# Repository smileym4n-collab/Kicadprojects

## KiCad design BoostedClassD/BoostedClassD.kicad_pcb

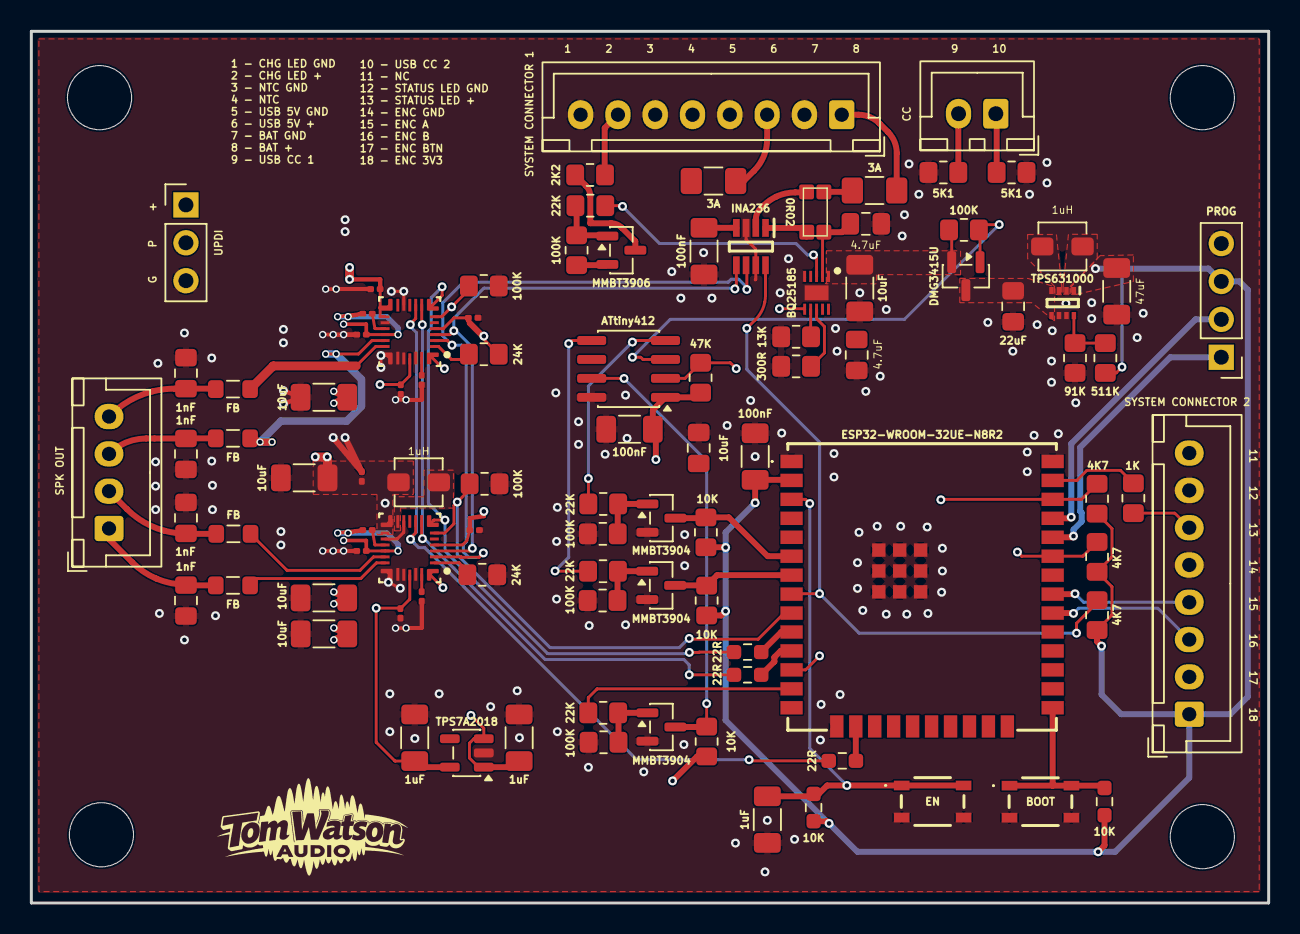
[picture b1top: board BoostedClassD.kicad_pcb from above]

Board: 4 copper layers, 82.9 x 58.4 mm, 99 parts (0 on the bottom side), 72 nets.

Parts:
C1: 22uF; C_0805_2012Metric_Pad1.18x1.45mm_HandSolder
C2: 47uF; C_1206_3216Metric_Pad1.33x1.80mm_HandSolder
C3, C7, C8: 100nF; C_1206_3216Metric_Pad1.33x1.80mm_HandSolder
C4, C5, C6: 1uF; C_1206_3216Metric_Pad1.33x1.80mm_HandSolder
C9, C10, C11, C12, C25: 10uF; C_1206_3216Metric_Pad1.33x1.80mm_HandSolder
C13, C14, C17, C18: 100nF; C_0201_0603Metric
C15, C16, C19, C20: 1uF; C_0201_0603Metric
C21, C22, C23, C24: 2.2uF; C_0201_0603Metric
C26, C27: 4.7uF; C_0805_2012Metric_Pad1.18x1.45mm_HandSolder
C28, C29, C30, C31: 1nF; C_0805_2012Metric_Pad1.18x1.45mm_HandSolder
C32: 10uF; C_0805_2012Metric_Pad1.18x1.45mm_HandSolder
F1, F2: 3A; Fuse_1206_3216Metric_Pad1.42x1.75mm_HandSolder
FB1, FB2, FB3, FB4: FB; L_0805_2012Metric_Pad1.05x1.20mm_HandSolder
H1, H2, H3, H4: MountingHole_4.3mm_M4
IC1: BQ25185; BQ25185DLHR
IC2: ESP32-WROOM-32UE-N8R2; ESP32WROOM32UEN8R2
IC5: INA236; INA236BIDDFR
J1: SYSTEM CONNECTOR 1; JST_XH_B8B-XH-A_1x08_P2.50mm_Vertical
J2: SYSTEM CONNECTOR 2; JST_XH_B8B-XH-A_1x08_P2.50mm_Vertical
J3: SPK OUT; JST_XH_B4B-XH-A_1x04_P2.50mm_Vertical
J4: PROG; PinHeader_1x04_P2.54mm_Vertical
J5: CC; JST_XH_B2B-XH-A_1x02_P2.50mm_Vertical
J6: UPDI; PinHeader_1x03_P2.54mm_Vertical
L1, L2: 1uH; L_Vishay_IHLP-1212
Q1: DMG3415U; SOT-23
Q2, Q3, Q4: MMBT3904; SOT-23
Q5: MMBT3906; SOT-23
R1, R2: 10K; R_0603_1608Metric_Pad0.98x0.95mm_HandSolder
R3, R4, R5: 22R; R_0603_1608Metric_Pad0.98x0.95mm_HandSolder
R6: 91K; R_0805_2012Metric_Pad1.20x1.40mm_HandSolder
R7: 511K; R_0805_2012Metric_Pad1.20x1.40mm_HandSolder
R8, R12, R33: 4K7; R_0805_2012Metric_Pad1.20x1.40mm_HandSolder
R9: 0R02; Untitled_4
R13: 47K; R_0805_2012Metric_Pad1.20x1.40mm_HandSolder
R14, R15, R32: 10K; R_0805_2012Metric_Pad1.20x1.40mm_HandSolder
R16, R22, R23, R27, R29, R31, R36: 100K; R_0805_2012Metric_Pad1.20x1.40mm_HandSolder
R17: 300R; R_0805_2012Metric_Pad1.20x1.40mm_HandSolder
R18: 13K; R_0805_2012Metric_Pad1.20x1.40mm_HandSolder
R19: 2K2; R_0805_2012Metric_Pad1.20x1.40mm_HandSolder
R20, R21: 5K1; R_0805_2012Metric_Pad1.20x1.40mm_HandSolder
R24, R25: 24K; R_0805_2012Metric_Pad1.20x1.40mm_HandSolder
R26, R28, R30, R35: 22K; R_0805_2012Metric_Pad1.20x1.40mm_HandSolder
R34: 1K; R_0805_2012Metric_Pad1.20x1.40mm_HandSolder
S1: BOOT; PTS810SJM250SMTRLFS
S2: EN; PTS810SJM250SMTRLFS
U1: TPS631000
U2: TAS2320; TAS2120
U3: TAS2120
U4: TPS7A2018; SOT-23-5
U5: ATtiny412; SOIC-8_3.9x4.9mm_P1.27mm

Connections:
/ALERT_N: IC2.8 (IO32), IC5.8 (ALERT), R33.2
/AMP2120_SDZ: IC2.9 (IO33), R22.1, U3.7 (SD_N)
/Amplifiers/ADDR2120: R24.1, U3.2 (HW_SEL4_AD1)
/Amplifiers/ADDR2320: R25.1, U2.2 (HW_SEL4_AD1)
/Amplifiers/AMP2320_SDZ: IC2.12 (IO27), R23.1, U2.7 (SD_N)
/Amplifiers/BCK: R4.1, U2.9 (SBCLK), U3.9 (SBCLK)
/Amplifiers/DATA: R5.1, U2.10 (SDIN), U3.10 (SDIN)
/Amplifiers/LEFT+: FB3.1, U3.20 (OUTP)
/Amplifiers/LEFT-: FB4.1, U3.19 (OUTN)
/Amplifiers/LRCK: R3.1, U2.8 (FSYNC), U3.8 (FSYNC)
/Amplifiers/PVDD: C10.1, C11.1, C12.1, C13.1, C14.1, C17.2, C18.2, U2.18 (PVDD), U3.18 (PVDD)
/Amplifiers/SCL: IC2.36 (IO22), IC5.5 (SCL), R8.2, U2.4 (HW_SEL2_SCL), U3.4 (HW_SEL2_SCL)
/Amplifiers/SDA: IC2.33 (IO21), IC5.6 (SDA), R12.2, U2.3 (HW_SEL3_SDA), U3.3 (HW_SEL3_SDA)
/Amplifiers/SEL5: U2.1 (HW_SEL5_CLASSH_CTRL), U3.1 (HW_SEL5_CLASSH_CTRL)
/Amplifiers/SYS: C1.1, C6.1, C9.1, C19.1, C20.1, L2.1, Q1.3 (D), U1.4 (VIN), U1.5 (EN), U2.14 (VBAT), U2.15 (VBAT), U3.14 (VBAT_SNS), U3.15 (VBAT), U4.1 (IN), U4.3 (EN)
/Amplifiers/VDD1V8: C5.1, C21.1, C23.1, U2.24 (AVDD), U3.24 (AVDD), U4.5 (OUT)
/BAT +: F1.1, R9.1
/BQ-SYS: C8.1, C25.1, IC1.1 (SYS), J6.1, Q1.2 (S), Q5.2 (E), R13.1, R16.2, R32.1, R36.1, U5.1 (VCC)
/CHG LED +: J1.7, R19.2
/CHGPOWER/IN+: IC5.1 (IN+), R9.3
/CHGPOWER/IN-: IC5.2 (IN-), R9.2
/CHGPOWER/POWER-ON-MOSFET: Q1.1 (G), R16.1, U5.3 (PA7)
/CHGPOWER/STAT2_N: IC1.3 (STAT2), R35.1
/ENC A: IC2.31 (IO19), J2.4
/ENC B: IC2.30 (IO18), J2.3
/ENC BTN: J2.2, R13.2, U5.2 (PA6)
/ESP3V3: C2.1, C3.1, C7.1, C22.1, C24.1, IC2.2 (3V3), IC5.4 (VS), J2.1, J4.3, R1.1, R2.1, R7.1, R8.1, R12.1, R14.1, R15.1, R25.2, R33.1, U1.1 (VOUT), U2.5 (IOVDD), U3.5 (IOVDD)
/ESP32-ATTINY/ACK_N: Q4.3 (C), R32.2, U5.7 (PA3)
/ESP32-ATTINY/EN: C4.1, IC2.3 (EN), R1.2, S2.1 (NO_1), S2.2 (NO_2)
/ESP32-ATTINY/GPIO0: IC2.25 (IO0), R2.2, S1.1 (NO_1), S1.2 (NO_2)
/ESP32-ATTINY/OFF_REQ_DRIVE: R28.1, U5.5 (PA2)
/ESP32-ATTINY/PLAY_DRIVE: R26.1, U5.4 (PA1)
/ESP32-ATTINY/PLAY_PAUSE: IC2.6 (IO34), Q2.3 (C), R14.2
/ESP32-ATTINY/POWER_OFF_REQ: IC2.7 (IO35), Q3.3 (C), R15.2
/ESP32-ATTINY/PROG: J6.2, U5.6 (~RESET/PA0)
/ESP32-ATTINY/RX: IC2.34 (RXD0), J4.1
/ESP32-ATTINY/SHUTDOWN_ACK: IC2.13 (IO14), R30.1
/ESP32-ATTINY/TX: IC2.35 (TXD0), J4.2
/LEFT +: C30.1, FB3.2, J3.1
/LEFT -: C31.2, FB4.2, J3.2
/NTC +: IC1.6 (TS/MR), J1.5
/RIGHT +: C28.1, FB1.2, J3.4
/RIGHT -: C29.2, FB2.2, J3.3
/STATUS LED +: J2.6, R34.2
/USB5V +: C26.1, F2.1, IC1.10 (IN)
GND: C1.2, C2.2, C3.2, C4.2, C5.2, C6.2, C7.2, C8.2, C9.2, C10.2, C11.2, C12.2, C13.2, C14.2, C15.2, C16.2, C19.2, C20.2, C21.2, C22.2, C23.2, C24.2, C25.2, C26.2, C27.2, C28.2, C29.1, C30.2, C31.1, C32.2, IC1.4 (~CE), IC1.5 (GND), IC1.11 (EP), IC2.1 (GND_1), IC2.15 (GND_2), IC2.38 (GND_3), IC2.39 (GND_4), IC2.40 (GND_5), IC2.41 (GND_6), IC2.42 (GND_7), IC2.43 (GND_8), IC2.44 (GND_9), IC2.45 (GND_10), IC2.46 (GND_11), IC2.47 (GND_12), IC5.3 (GND), IC5.7 (A0), J1.2, J1.4, J1.6, J1.8, J2.5, J2.7, J4.4, J6.3, Q2.2 (E), Q3.2 (E), Q4.2 (E), R6.2, R17.1, R18.1, R20.1, R21.1, R22.2, R23.2, R24.2, R27.2, R29.2, R31.2, S1.3 (COM_1), S1.4 (COM_2), S2.3 (COM_1), S2.4 (COM_2), U1.6 (MODE), U1.7 (GND), U2.12 (GND), U2.16 (HW_SEL1), U2.21 (PGND), U2.22 (GND), U2.23 (GND), U2.25 (GND), U3.12 (BGND), U3.16 (HW_SEL1), U3.21 (PGND), U3.22 (GND), U3.23 (GND), U3.25 (GND), U4.2 (GND), U5.8 (GND)
unnamed: C27.1, IC1.2 (BAT), R9.4
unnamed: IC1.7 (ILIM/VSET), R18.2
unnamed: IC1.8 (ISET), R17.2
unnamed: IC2.16 (IO13), R5.2
unnamed: IC2.37 (IO23), R34.1
unnamed: IC2.10 (IO25), R3.2
unnamed: IC2.11 (IO26), R4.2
unnamed: F1.2, J1.1
unnamed: F2.2, J1.3
unnamed: J5.1, R20.2
unnamed: J5.2, R21.2
unnamed: Q2.1 (B), R26.2, R27.1
unnamed: Q3.1 (B), R28.2, R29.1
unnamed: Q4.1 (B), R30.2, R31.1
unnamed: Q5.1 (B), R35.2, R36.2
unnamed: Q5.3 (C), R19.1
unnamed: R6.1, R7.2, U1.8 (FB)
unnamed: L1.2, U1.3 (LX1)
unnamed: L1.1, U1.2 (LX2)
unnamed: C15.1, U2.26 (DREG)
unnamed: C18.1, U2.17 (GREG)
unnamed: FB2.1, U2.19 (OUTN)
unnamed: FB1.1, U2.20 (OUTP)
unnamed: C16.1, U3.26 (DREG)
unnamed: C17.1, U3.17 (GREG)
unnamed: L2.2, U3.13 (SW)

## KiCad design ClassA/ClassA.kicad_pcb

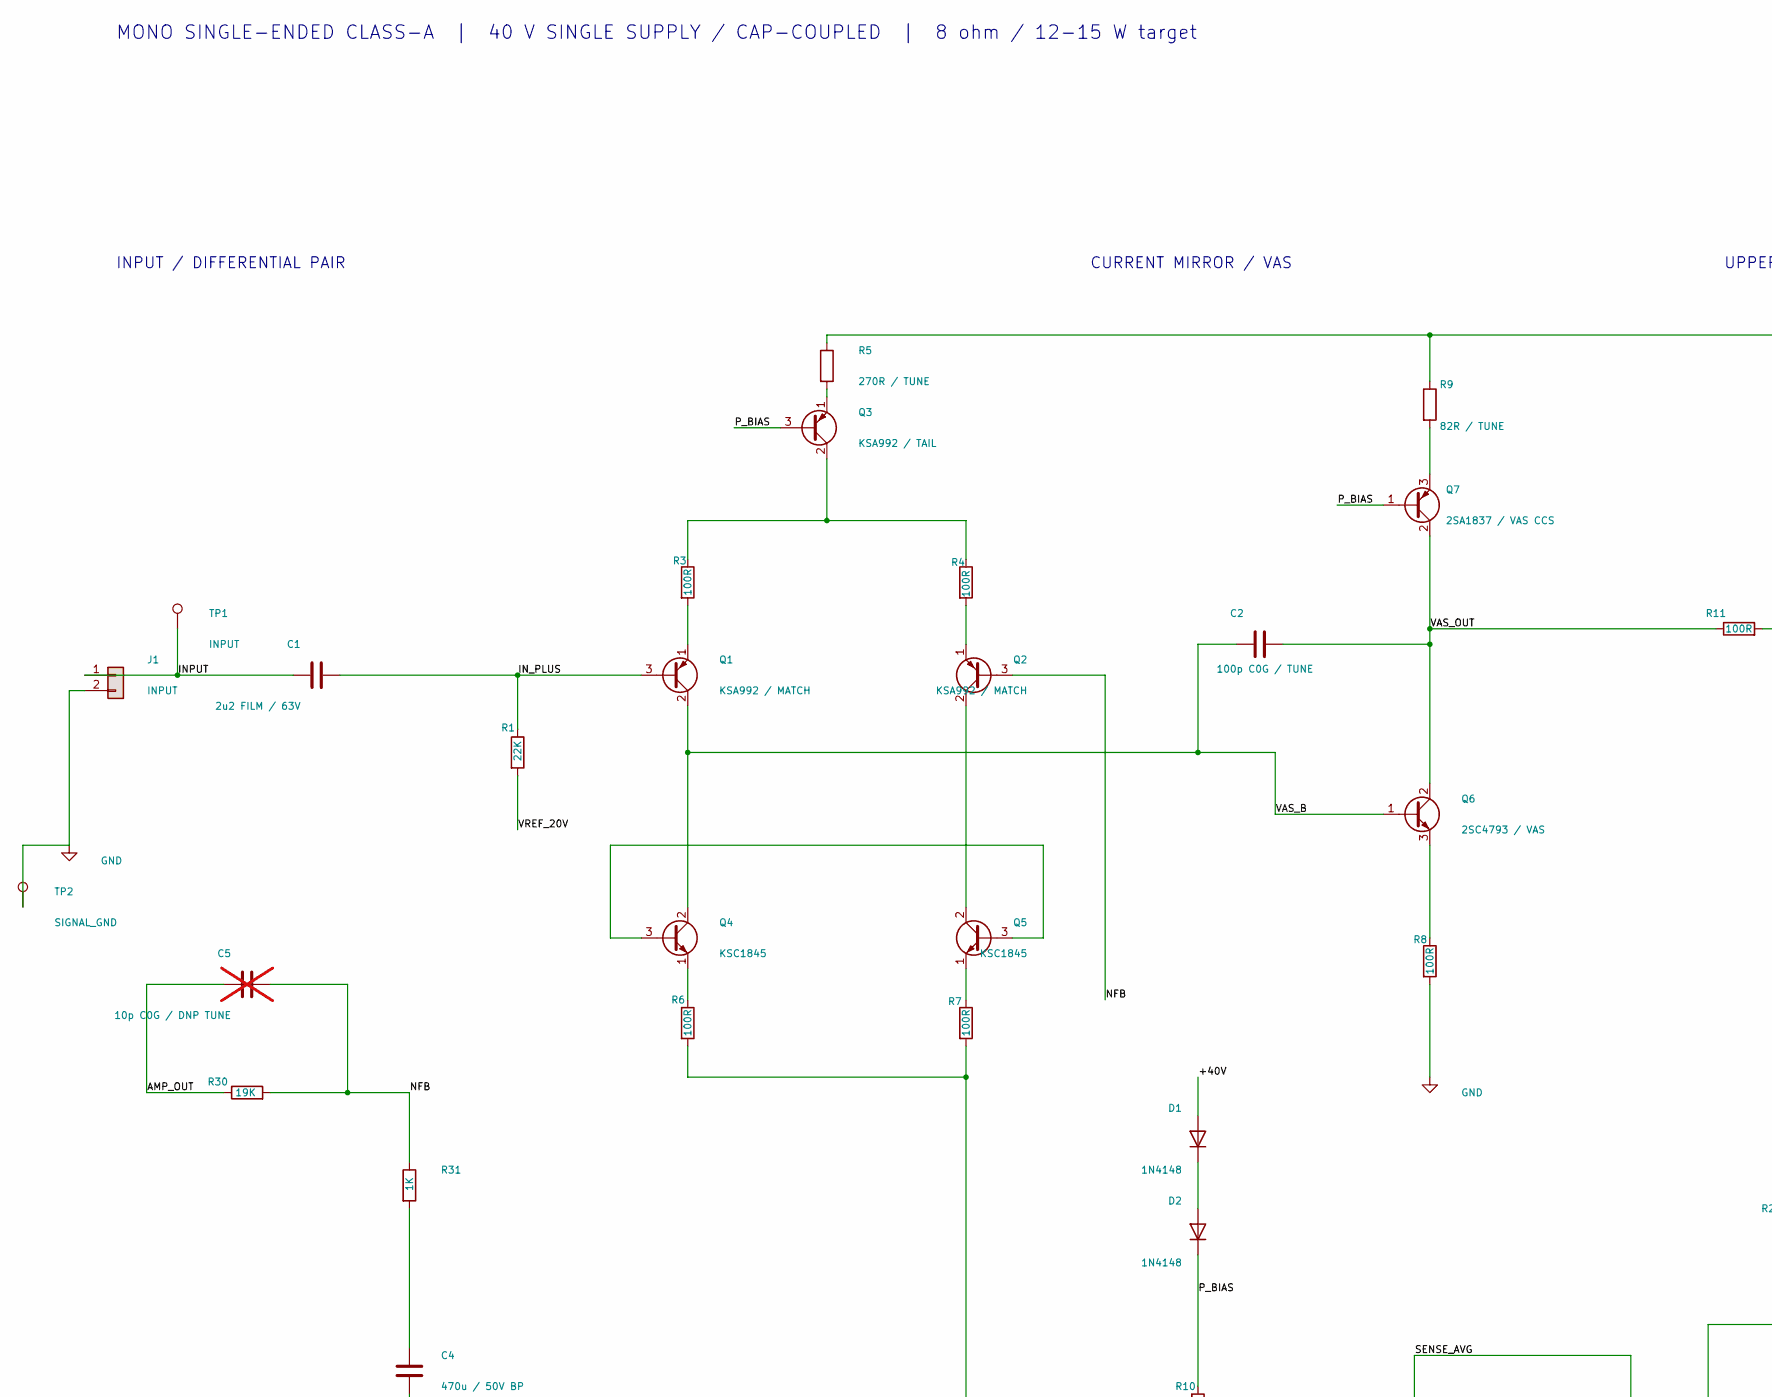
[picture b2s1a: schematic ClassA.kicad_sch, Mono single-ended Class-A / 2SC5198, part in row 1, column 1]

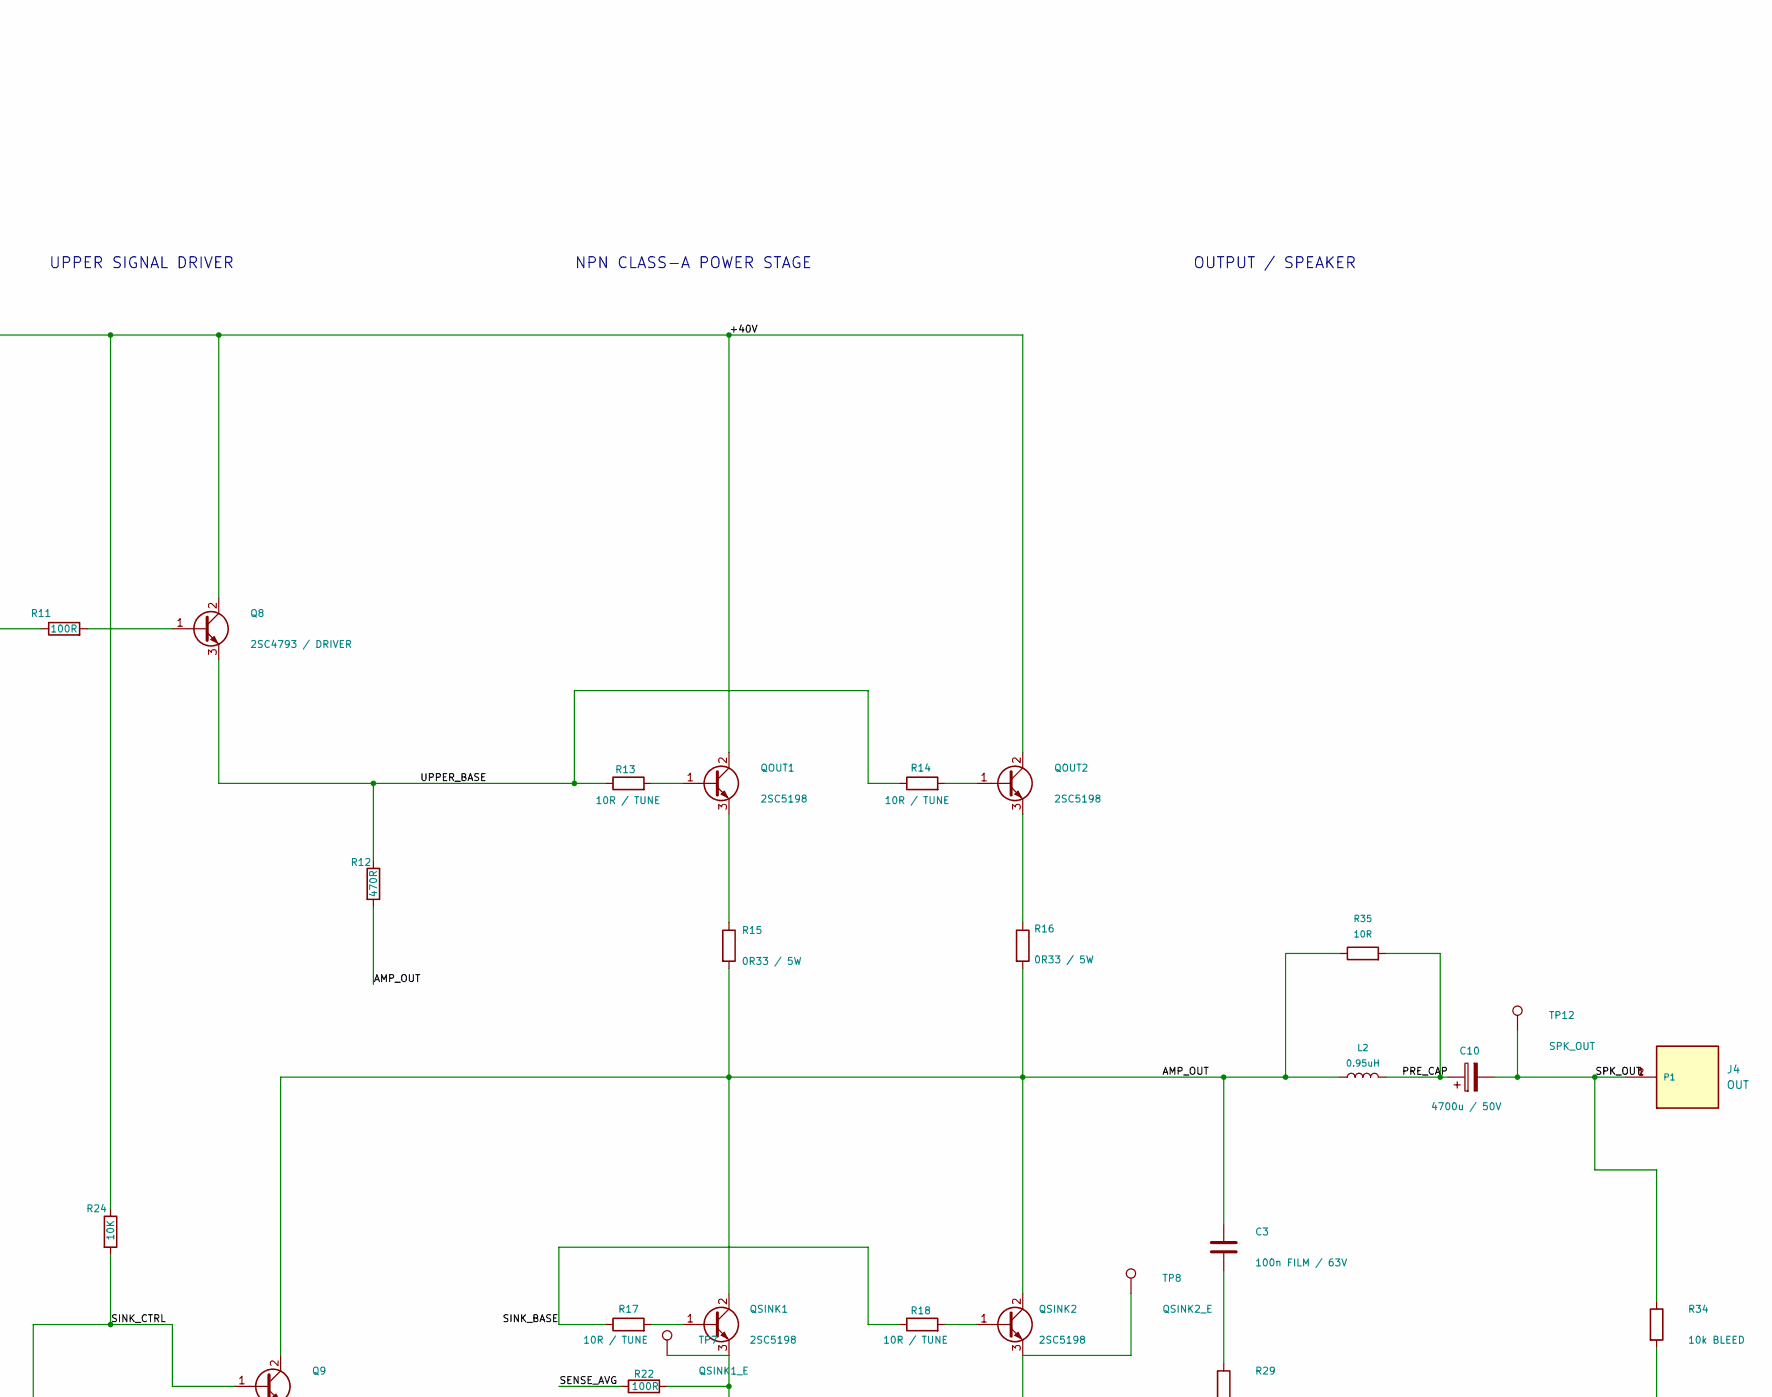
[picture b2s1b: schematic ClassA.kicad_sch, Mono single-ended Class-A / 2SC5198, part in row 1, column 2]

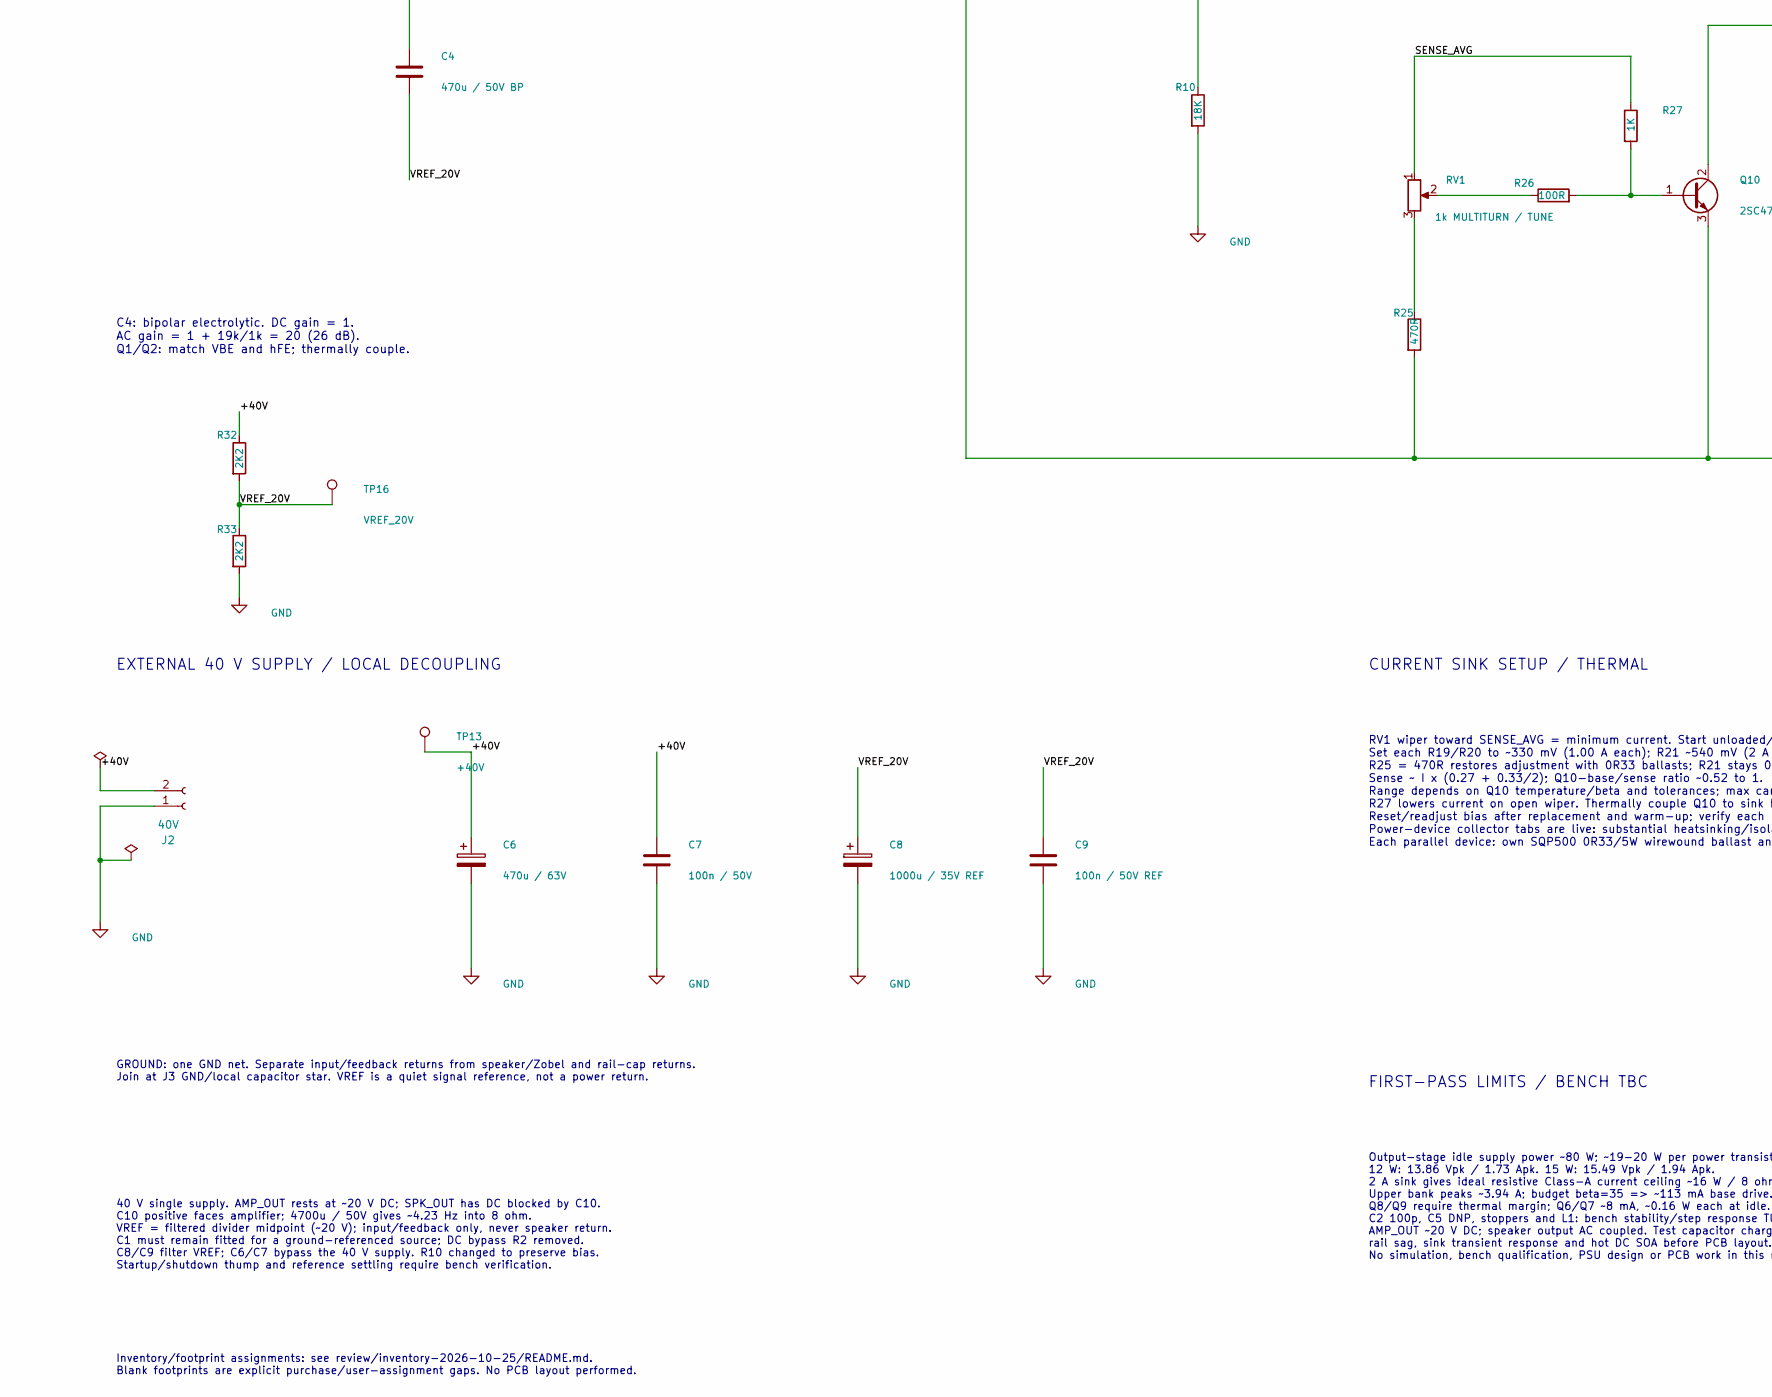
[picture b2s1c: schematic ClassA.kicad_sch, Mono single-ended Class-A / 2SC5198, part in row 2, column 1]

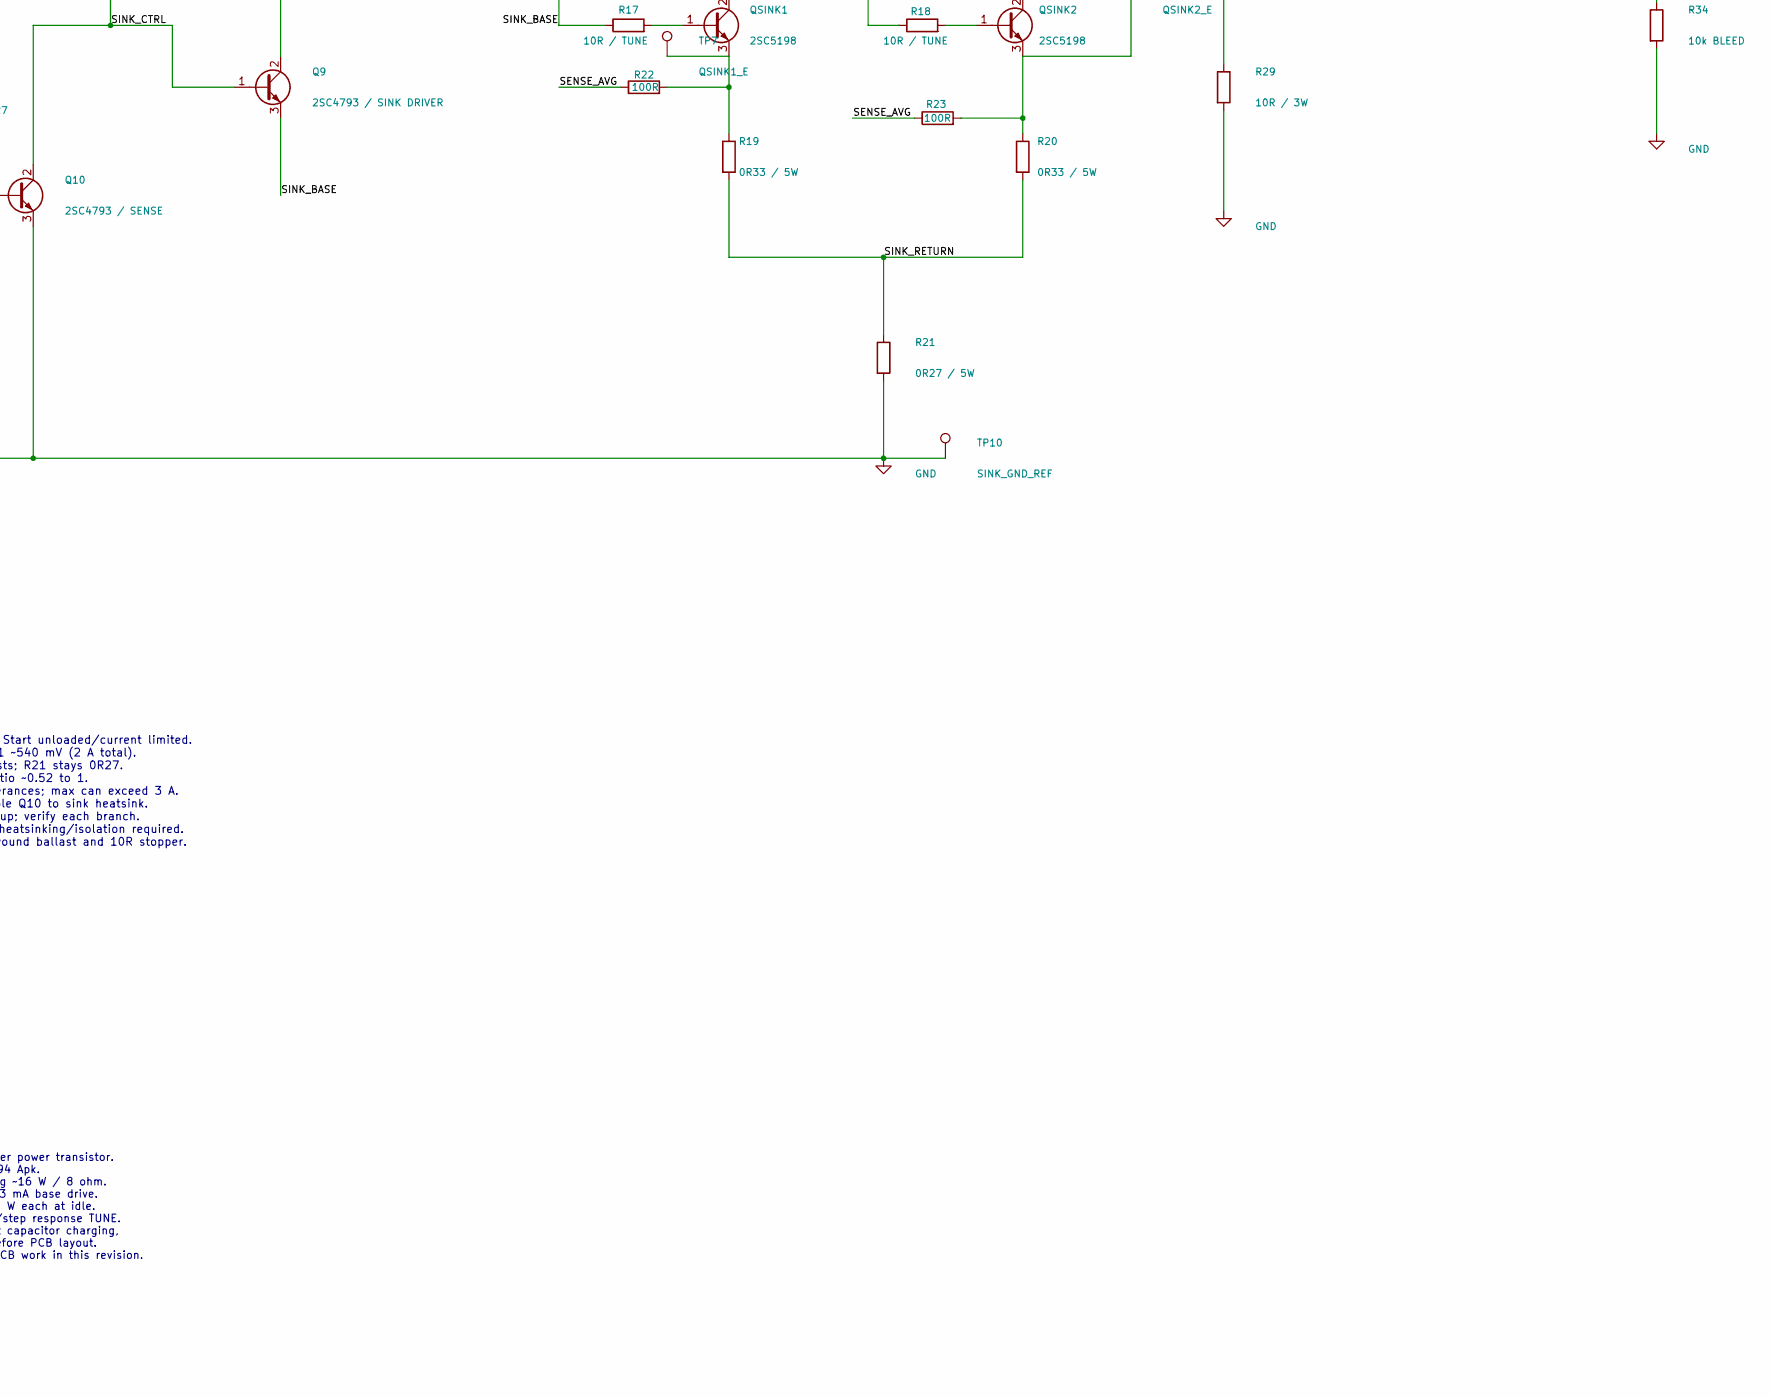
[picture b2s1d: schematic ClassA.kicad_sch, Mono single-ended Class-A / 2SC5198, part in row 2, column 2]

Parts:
C1: 2u2 FILM / 63V; C_Rect_L7.2mm_W7.2mm_P5.00mm; MPN MKS2C042201K00KSSD
C2: 100p C0G / TUNE; C_0805_2012Metric; MPN CL21C101JBANNNC
C3: 100n FILM / 63V; C_Rect_L7.2mm_W2.5mm_P5.00mm; MPN R82DC3100DQ50J
C4: 470u / 50V BP
C5: 10p C0G / DNP TUNE; C_0805_2012Metric; not fitted
C6: 470u / 63V
C7: 100n / 50V; C_1206_3216Metric; MPN C1206C104K5RACTU
C8: 1000u / 35V REF; CP_Radial_D12.5mm_P5.00mm; MPN EEUFR1V102
C9: 100n / 50V REF; C_1206_3216Metric; MPN C1206C104K5RACTU
C10: 4700u / 50V; CP_Radial_D22.0mm_P10.00mm_SnapIn; MPN MCGPR50V478M22X41
D1, D2: 1N4148; D_DO-35_SOD27_P7.62mm_Horizontal; MPN 1N4148
J1: INPUT; Multicomp_MC34629_1x02_P2.54mm; MPN MC34629
J2: 40V; Molex_KK-396_5273-02A_1x02_P3.96mm_Vertical; Manufacturer_Part_Number 09-65-2028
J4: OUT; TE_62409-1; PART_DESCRIPTION CONN QC TAB 0.250 SOLDER
L2: 0.95uH; L_Yamaha_L505_15x15mm_P12mm
Q1, Q2: KSA992 / MATCH; TO-92_Wide; MPN KSA992FTA
Q3: KSA992 / TAIL; TO-92_Wide; MPN KSA992FTA
Q4, Q5: KSC1845; TO-92_Wide; MPN KSC1845FTA
Q6: 2SC4793 / VAS; TO-220F-3_Vertical; MPN 2SC4793
Q7: 2SA1837 / VAS CCS; TO-220F-3_Vertical; MPN 2SA1837
Q8: 2SC4793 / DRIVER; TO-220F-3_Vertical; MPN 2SC4793
Q9: 2SC4793 / SINK DRIVER; TO-220F-3_Vertical; MPN 2SC4793
Q10: 2SC4793 / SENSE; TO-220F-3_Vertical; MPN 2SC4793
QOUT1, QOUT2: 2SC5198; TO-3P-3_Vertical; MPN 2SC5198
QSINK1, QSINK2: 2SC5198; TO-3P-3_Vertical; MPN 2SC5198
R1: 22K; R_0805_2012Metric; MPN RR1220P-223-D
R3, R4, R6, R7, R8, R11, R22, R23, R26: 100R; R_0805_2012Metric; MPN RR1220P-101-D
R5: 270R / TUNE; R_Axial_DIN0207_L6.3mm_D2.5mm_P10.16mm_Horizontal; MPN LR1F270R
R9: 82R / TUNE; R_0805_2012Metric
R10: 18K; R_Axial_DIN0207_L6.3mm_D2.5mm_P10.16mm_Horizontal; MPN LR1F18K
R12: 470R; R_Axial_DIN0207_L6.3mm_D2.5mm_P10.16mm_Horizontal; MPN LR1F470R
R13, R14, R17, R18: 10R / TUNE; R_Axial_DIN0207_L6.3mm_D2.5mm_P10.16mm_Horizontal; MPN LR1F10R
R15, R16, R19, R20: 0R33 / 5W; Yageo_SQP500_L22.0mm_W9.5mm_P30.48mm; MPN SQP500JB-0R33
R21: 0R27 / 5W
R24: 10K; R_Axial_DIN0207_L6.3mm_D2.5mm_P10.16mm_Horizontal; MPN LR1F10K
R25: 470R; R_0805_2012Metric; MPN ASC0805-470RFT5
R27, R31: 1K; R_0805_2012Metric; MPN RR1220P-102-D
R29: 10R / 3W
R30: 19K; R_0805_2012Metric
R32, R33: 2K2; R_Axial_DIN0207_L6.3mm_D2.5mm_P10.16mm_Horizontal; MPN LR1F2K2
R34: 10k BLEED; R_Axial_DIN0207_L6.3mm_D2.5mm_P10.16mm_Horizontal; MPN LR1F10K
R35: 10R; R_Axial_DIN0414_L11.9mm_D4.5mm_P15.24mm_Horizontal; Manufacturer_Part_Number RSMF2JT10R0
RV1: 1k MULTITURN / TUNE
TP1: INPUT; TestPoint_THTPad_D1.5mm_Drill0.7mm
TP2: SIGNAL_GND; TestPoint_THTPad_D1.5mm_Drill0.7mm
TP7: QSINK1_E; TestPoint_THTPad_D1.5mm_Drill0.7mm
TP8: QSINK2_E; TestPoint_THTPad_D1.5mm_Drill0.7mm
TP10: SINK_GND_REF; TestPoint_THTPad_D1.5mm_Drill0.7mm
TP12: SPK_OUT; TestPoint_THTPad_D1.5mm_Drill0.7mm
TP13: +40V; TestPoint_THTPad_D1.5mm_Drill0.7mm
TP16: VREF_20V; TestPoint_THTPad_D1.5mm_Drill0.7mm

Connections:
/+40V: C6.1, C7.1, D1.2 (A), J2.2, Q8.2 (C), QOUT1.2 (C), QOUT2.2 (C), R5.1, R9.1, R24.1, R32.1, TP13.1 (1_1)
/AMP_OUT: C3.1, C5.1, L2.1, Q9.2 (C), QSINK1.2 (C), QSINK2.2 (C), R12.2, R15.2, R16.2, R30.1, R35.1
/INPUT: C1.1, J1.1, TP1.1 (1_1)
/IN_PLUS: C1.2, Q1.3 (B), R1.1
/NFB: C5.2, Q2.3 (B), R30.2, R31.1
/PRE_CAP: C10.1, L2.2, R35.2
/P_BIAS: D2.1 (K), Q3.3 (B), Q7.1 (B), R10.1
/SENSE_AVG: R22.1, R23.1, R27.1, RV1.1
/SINK_BASE: Q9.3 (E), R17.1, R18.1
/SINK_CTRL: Q9.1 (B), Q10.2 (C), R24.2
/SINK_RETURN: R19.2, R20.2, R21.1
/SPK_OUT: C10.2, J4.1, J4.2 (P1), R34.1, TP12.1 (1_1)
/UPPER_BASE: Q8.3 (E), R12.1, R13.1, R14.1
/VAS_B: C2.1, Q1.2 (C), Q4.2 (C), Q6.1 (B)
/VAS_OUT: C2.2, Q6.2 (C), Q7.2 (C), R11.1
/VREF_20V: C4.2, C8.1, C9.1, R1.2, R32.2, R33.1, TP16.1 (1_1)
GND: C6.2, C7.2, C8.2, C9.2, J1.2, J2.1, Q10.3 (E), R6.2, R7.2, R8.2, R10.2, R21.2, R25.2, R29.2, R33.2, R34.2, TP2.1 (1_1), TP10.1 (1_1)
unnamed: C3.2, R29.1
unnamed: C4.1, R31.2
unnamed: D1.1 (K), D2.2 (A)
unnamed: Q1.1 (E), R3.2
unnamed: Q2.2 (C), Q5.2 (C)
unnamed: Q2.1 (E), R4.2
unnamed: Q3.2 (C), R3.1, R4.1
unnamed: Q3.1 (E), R5.2
unnamed: Q4.3 (B), Q5.3 (B)
unnamed: Q4.1 (E), R6.1
unnamed: Q5.1 (E), R7.1
unnamed: Q6.3 (E), R8.1
unnamed: Q7.3 (E), R9.2
unnamed: Q8.1 (B), R11.2
unnamed: Q10.1 (B), R26.2, R27.2
unnamed: QOUT1.1 (B), R13.2
unnamed: QOUT1.3 (E), R15.1
unnamed: QOUT2.1 (B), R14.2
unnamed: QOUT2.3 (E), R16.1
unnamed: QSINK1.1 (B), R17.2
unnamed: QSINK1.3 (E), R19.1, R22.2, TP7.1 (1_1)
unnamed: QSINK2.1 (B), R18.2
unnamed: QSINK2.3 (E), R20.1, R23.2, TP8.1 (1_1)
unnamed: R25.1, RV1.3
unnamed: R26.1, RV1.2

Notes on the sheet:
40 V single supply. AMP_OUT rests at ~20 V DC; SPK_OUT has DC blocked by C10. C10 positive faces amplifier; 4700u / 50V gives ~4.23 Hz into 8 ohm. VREF = filtered divider midpoint (~20 V); input/feedback only, never speaker return. C1 must remain fitted for a ground-referenced source; DC bypass R2 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
FIRST-PASS LIMITS / BENCH TBC
CURRENT MIRROR / VAS
OUTPUT / SPEAKER
NPN CLASS-A POWER STAGE
Inventory/footprint assignments: see review/inventory-2026-10-25/README.md. Blank footprints are explicit purchase/user-assignment gaps. No PCB layout performed.
EXTERNAL 40 V SUPPLY / LOCAL DECOUPLING
RV1 wiper toward SENSE_AVG = minimum current. Start unloaded/current limited. Set each R19/R20 to ~330 mV (1.00 A each); R21 ~540 mV (2 A total). R25 = 470R restores adjustment with 0R33 ballasts; R21 stays 0R27. Sense ~ I x (0.27 + 0.33/2); Q10-base/sense ratio ~0.52 to 1. Range depends on Q10 tem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
CURRENT SINK SETUP / THERMAL
C4: bipolar electrolytic. DC gain = 1. AC gain = 1 + 19k/1k = 20 (26 dB). Q1/Q2: match VBE and hFE; thermally couple.
UPPER SIGNAL DRIVER
GROUND: one GND net. Separate input/feedback returns from speaker/Zobel and rail-cap returns. Join at J3 GND/local capacitor star. VREF is a quiet signal reference, not a power return.
Output-stage idle supply power ~80 W; ~19-20 W per power transistor. 12 W: 13.86 Vpk / 1.73 Apk. 15 W: 15.49 Vpk / 1.94 Apk. 2 A sink gives ideal resistive Class-A current ceiling ~16 W / 8 ohm. Upper bank peaks ~3.94 A; budget beta=35 => ~113 mA base drive. Q8/Q9 require thermal margin; Q6/Q7 ~8 m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
MONO SINGLE-ENDED CLASS-A | 40 V SINGLE SUPPLY / CAP-COUPLED | 8 ohm / 12-15 W target
INPUT / DIFFERENTIAL PAIR

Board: 2 copper layers, 67 parts (1 on the bottom side), 38 nets, no tracks yet.

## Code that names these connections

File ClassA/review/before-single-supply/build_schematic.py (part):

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text('INPUT / DIFFERENTIAL PAIR',12,23,1.8);text('CURRENT MIRROR / VAS',75,23,1.8);text('UPPER SIGNAL DRIVER',116,23,1.8);text('NPN CLASS-A POWER STAGE',150,23,1.8);text('OUTPUT / SPEAKER',190,23,1.8)
# INPUT: default AC input; DNP jumper permits DC coupling.
j=inst(J2,'J1','INPUT',12,50);wire(j['1'],(16,50));label('INPUT',(16,50));tp('INPUT',(16,50))
c=two(C,'C1','2u2 FILM / 63V',25,50,True);wire((16,50),c['1']);wire(c['2'],(38,50));label('IN_PLUS',(38,50))
r=resistor('R1','22k / 1% thin-film',(38,50),(38,60));ground((38,60));wire(j['2'],(9,51),(9,61));ground((9,61));tp('SIGNAL_GND',(9,61),(-3,4))
r=resistor('R2','0R DC BYPASS / DNP',(20,43),(30,43));wire((20,50),(20,43));wire((30,43),(30,50));# actual DNP property below
# Differential PNP: input on active collector side, feedback on mirror reference side.
q1=inst(P,'Q1','KSA992 / MATCH',48,50,m='x',ds=DSKSA);q2=inst(P,'Q2','KSA992 / MATCH',68,50,a=180,ds=DSKSA)
wire((38,50),q1['3']);wire(q2['3'],(76,50),(76,71));label('NFB',(76,71));tp('NFB',(76,71),(3,0))
resistor('R3','100R',q1['1'],(49,40));resistor('R4','100R',q2['1'],(67,40));wire((49,40),(58,40),(67,40))
qt=inst(P,'Q3','KSA992 / TAIL',57,34,m='x',ds=DSKSA);wire(qt['2'],(58,40));resistor('R5','270R / TUNE',qt['1'],(58,28));label('+20V',(58,28));wire(qt['3'],(52,34));label('P_BIAS',(52,34))
# NPN current mirror at negative rail, active load on input-side collector.
qm1=inst(N,'Q4','KSC1845',48,67,ds=DSKSC);qm2=inst(N,'Q5','KSC1845',68,67,a=0,m='y',ds=DSKSC)
wire(q1['2'],(49,55),(49,65));wire(q2['2'],(67,56),(67,65));wire(qm1['3'],(44,67),(44,61),(58,61),(72,61),(72,67),qm2['3']);wire((67,61),(67,65))
resistor('R6','100R',qm1['1'],(49,76));resistor('R7','100R',qm2['1'],(67,76));wire((49,76),(67,76));label('-20V',(58,76))
# VAS and 8 mA PNP active load; reference is shared with tail.
qv=inst(MED,'Q6','2SC4793 / VAS',96,59,ds=DS4793);wire((49,55),(87,55),(87,59),qv['1']);label('VAS_B',(87,59));resistor('R8','100R',qv['3'],(97,76));label('-20V',(97,76))
ql=inst(PMED,'Q7','2SA1837 / VAS CCS',96,39,m='x',ds=DS1837);resistor('R9','82R / TUNE',ql['3'],(97,28));label('+20V',(97,28));wire(ql['1'],(91,39));label('P_BIAS',(91,39));wire(ql['2'],(97,47),qv['2']);label('VAS_OUT',(97,47))
c=two(C,'C2','100p C0G / TUNE',86,48,True);wire(c['1'],(82,48),(82,55));wire(c['2'],(97,48));
# Positive reference: two silicon junctions, 2 mA bias. KSA tail and VAS current decrease with heat.
resistor('R10','9k1 / 0.25W',(82,90),(82,105));ground((82,105))
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# Diodes horizontal by default, rotate90 for cathode downward.
# Replaced below by helpers using parsed pin positions.
# upper driver
qd=inst(MED,'Q8','2SC4793 / DRIVER',126,47,ds=DS4793);resistor('R11','100R',(110,47),qd['1']);wire((97,47),(110,47));wire(qd['2'],(127,28));label('+20V',(127,28));wire(qd['3'],(127,57),(140,57));label('UPPER_BASE',(140,57))
resistor('R12','470R', (137,57),(137,70));label('AMP_OUT',(137,70));
# Output transistors QOUT1/2: vertical emitter followers, all local connections visible.
a=inst(POW,'QOUT1','2SC5198',159,57,ds=DS5198);b=inst(POW,'QOUT2','2SC5198',178,57,ds=DS5198)
wire((160,28),(179,28));label('+20V',(160,28));wire(a['2'],(160,28));wire(b['2'],(179,28))
resistor('R13','10R / TUNE',(150,57),a['1']);resistor('R14','10R / TUNE',(169,57),b['1']);wire((140,57),(150,57));wire((150,57),(150,51),(169,51),(169,57))
resistor('R15','0R22 / 5W',a['3'],(160,76));resistor('R16','0R22 / 5W',b['3'],(179,76));wire((160,76),(179,76),(188,76));label('AMP_OUT',(188,76));tp('AMP_OUT',(188,76));tp('QOUT1_E',(160,60),(-4,0));tp('QOUT2_E',(179,60),(4,0))
# Lower sink transistors share collector node ONLY. Their drive is DC current regulation.
sa=inst(POW,'QSINK1','2SC5198',159,92,ds=DS5198);sb=inst(POW,'QSINK2','2SC5198',178,92,ds=DS5198);wire(sa['2'],(160,76));wire(sb['2'],(179,76))
resistor('R17','10R / TUNE',(150,92),sa['1']);resistor('R18','10R / TUNE',(169,92),sb['1']);wire((150,92),(150,87),(169,87),(169,92));label('SINK_BASE',(150,92))
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# Average individual emitter voltages then sense against negative rail. Req = .27 + .22/2.
resistor('R22','100R / 1%',(149,96),(160,96));resistor('R23','100R / 1%',(168,98),(179,98));wire((179,98),(179,96));label('SENSE_AVG',(149,96));label('SENSE_AVG',(168,98))
# Current-sink feedback placed beneath VAS/driver.
qsd=inst(MED,'Q9','2SC4793 / SINK DRIVER',130,96,ds=DS4793);wire(qsd['2'],(131,84));label('AMP_OUT',(131,84));wire(qsd['3'],(131,103));label('SINK_BASE',(131,103))
resistor('R24','10k / 0.5W',(120,80),(120,92));label('+20V',(120,80));wire((120,92),(124,92),(124,96),qsd['1']);label('SINK_CTRL',(120,92))
qs=inst(MED,'Q10','2SC4793 / SENSE',114,103,ds=DS4793);wire(qs['2'],(115,92),(120,92));wire(qs['3'],(115,120));label('-20V',(115,120));tp('CS_VBE',(110,103),(-2,-3))
# Pot 1 at upper end SENSE_AVG, 3 at lower end, wiper2 through100 to sense base.
pot=inst(POT,'RV1','1k MULTITURN / TUNE',96,103);resistor('R25','3k3',pot['3'],(96,120));label('-20V',(96,120));wire(pot['1'],(96,94));label('SENSE_AVG',(96,94));resistor('R26','100R',pot['2'],qs['1']);resistor('R27','1k FAIL-LOW',(110,94),(110,103));wire((110,94),(96,94));wire((110,103),qs['1'])
# Output stability network; feedback before series inductor.
ind=two(L,'L1','0.82uH / >=4A / TBC',201,76,True);wire((188,76),ind['1']);wire(ind['2'],(216,76));label('SPK_OUT',(216,76));tp('SPK_OUT',(211,76))
resistor('R28','10R / 3W',(196,68),(206,68));wire((196,68),(196,76));wire((206,68),(206,76));j=inst(J2,'J2','SPEAKER / 8 ohm',220,76);wire((216,76),j['1']);wire(j['2'],(214,77),(214,96));ground((214,96))
cz=two(C,'C3','100n FILM / 63V',192,87);wire((192,76),cz['1']);resistor('R29','10R / 3W',cz['2'],(192,104));ground((192,104))
# Feedback dc gain unity, ac gain20; electrolytic pole .34Hz. DC offset matching at unity.
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for ref in ['D1','D2']:
 idx=next(i for i,s in enumerate(parts) if f'(property "Reference" "{ref}"' in s);parts.pop(idx);comps.pop(ref)
d1=inst(D,'D1','1N4148',82,80,a=90);d2=inst(D,'D2','1N4148',82,86,a=90)
wire(d1['2'],(82,76));label('+20V',(82,76));wire(d1['1'],d2['2']);wire(d2['1'],(82,90));label('P_BIAS',(82,90))
# Explicit DC bypass DNP.
for i,s in enumerate(parts):
 if '(property "Reference" "R2"' in s:parts[i]=s.replace('(dnp no)','(dnp yes)')
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

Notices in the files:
BoostedClassD/BoostedClassD.kicad_pcb:
© Tom Watson Audio 2026
